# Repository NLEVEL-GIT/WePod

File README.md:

# WePod

Wepod is Our Ipod, it is an open source MP3 Player that uses the Xiao RP2040

PS: All images of the PCB, CAD and Schematics are on the assets folder if u wanna see.

## Features:
- 1.3 Inch TFT Display
- 5 Button
- SD Card Reader
- 3.5mm Jack
- Powered by any 5V Supply using the dedicated pads

## CAD Model:
Everything fits in a sandwich kind of way by stacking the bottom and top case parts and inbetween the PCB. It requires 4 M3x3 brass inserts and 4 15mm M3 Screws.
It has 3 different printed pieces. The Bottom part of the case where everything will sit in. The Top part that locks everything and the Butons (5 Needed).
Made in Fusion360 cuz its free.

## PCB
It was made in KiCad. Only needing to add Kicad Care package Symbols and Footprints for the Xiao RP2040 and a bunch of other symbols found in SnapEDA.
All 3D models were found on GrabCad

**Schematic:**

**PCB Layout:**

## Firmware Overview
The WePod uses C++ as its language of choice and it was made with the help of generative AI since im not really good at coding.

## BOM:
Here should be everything you need to make this hackpad

- 1.3 Inch TFT display
- DFPlayer
- 3.5mm Jack
- 5x 6x6mm buttons
- 1x XIAO RP2040
- 1x Case (3 printed parts)
- A Bunch of Resistors (1k, 3.3k, 6.8k, 10k and 100k)
- 2x 10uf Capacitors

## Extra stuff
This was my first Original project since my first was the MacroPad so not using a siplified code made me want to die. Conclusion: Hardware is life and coding Sucks

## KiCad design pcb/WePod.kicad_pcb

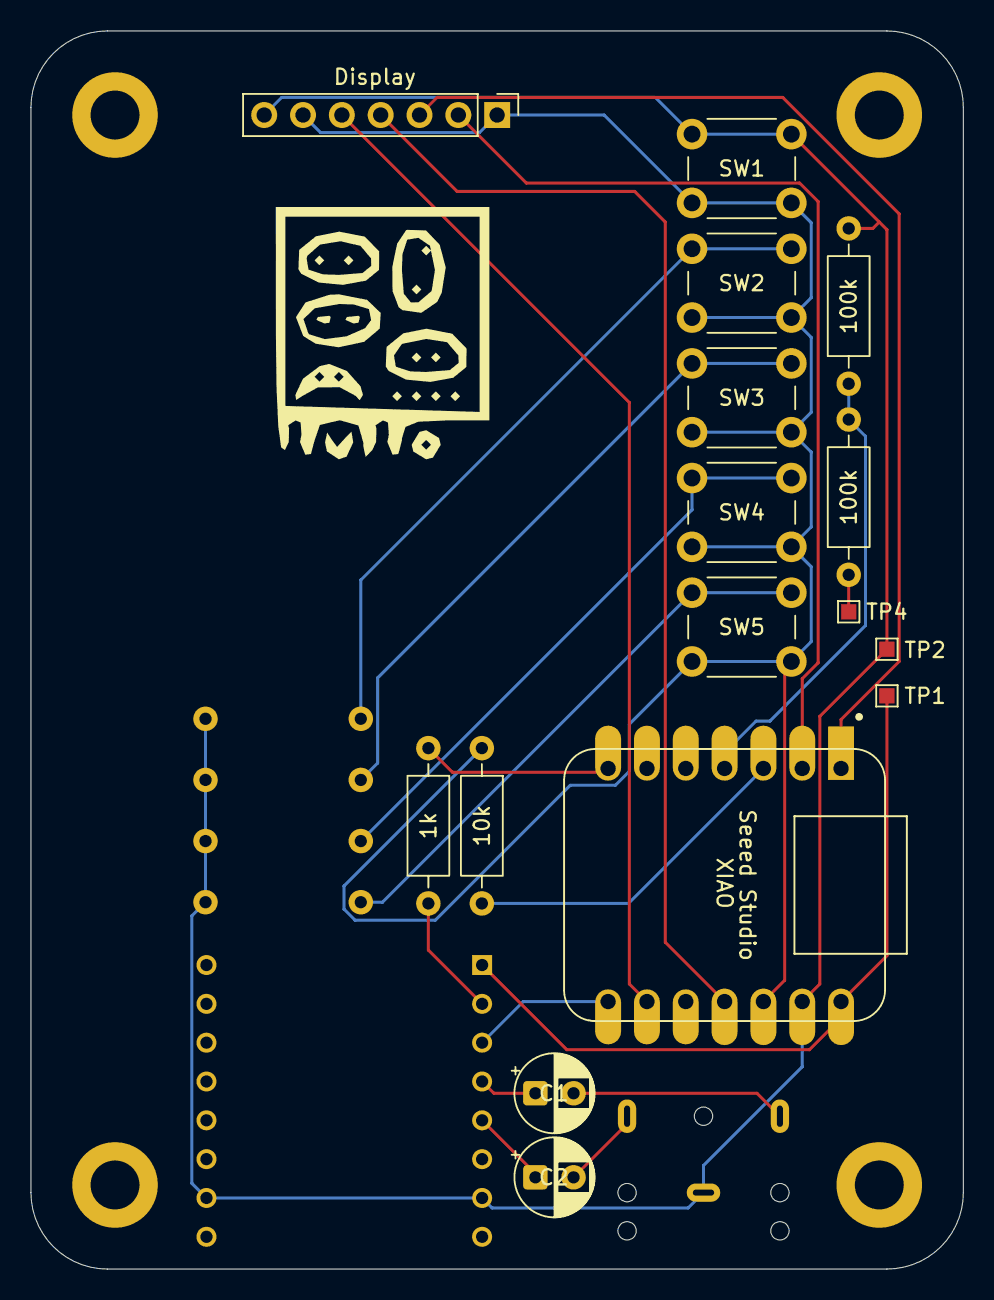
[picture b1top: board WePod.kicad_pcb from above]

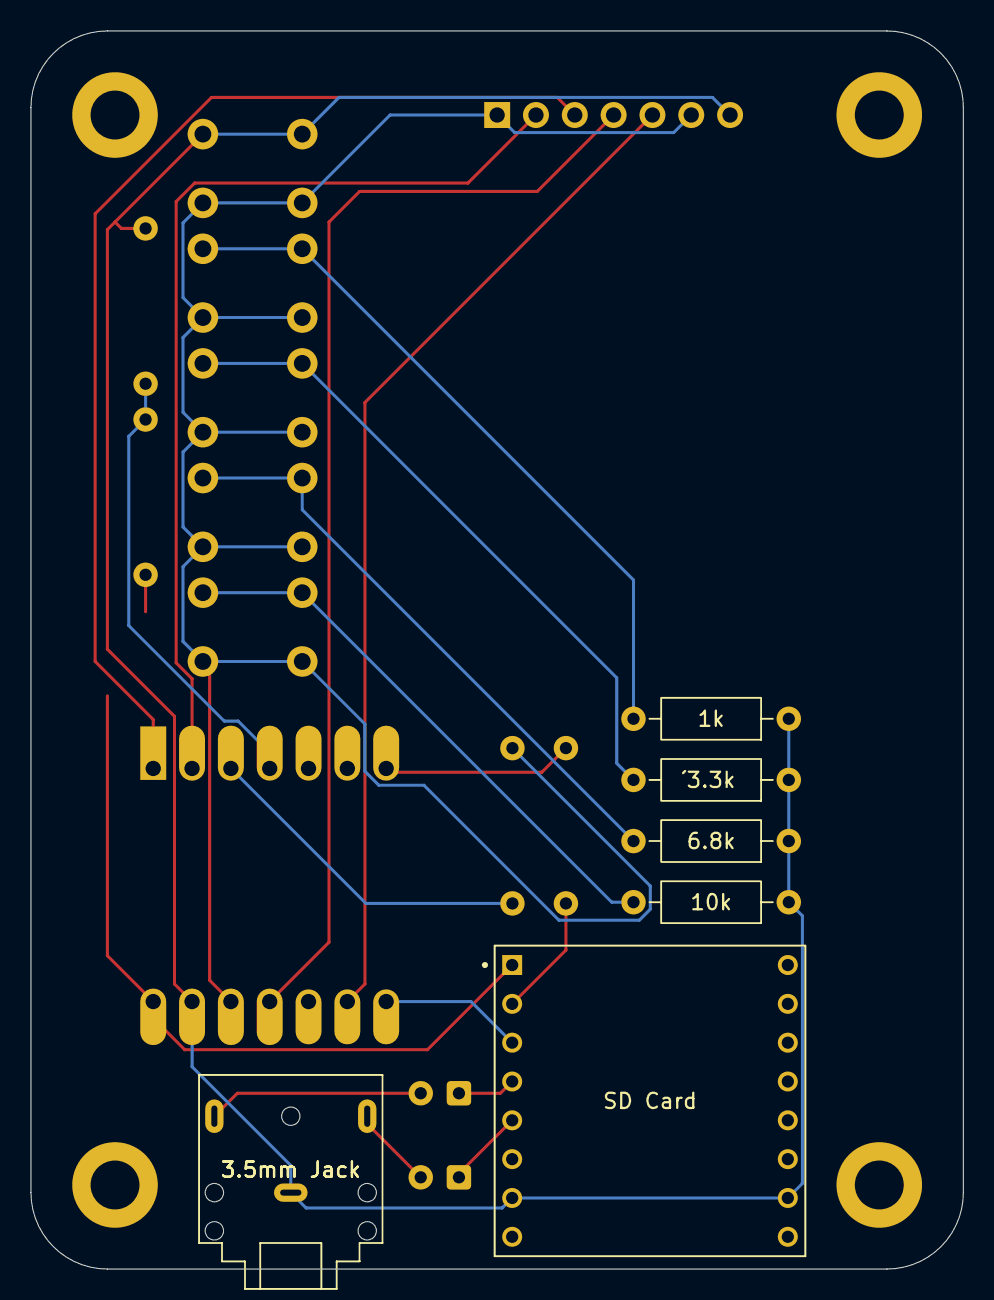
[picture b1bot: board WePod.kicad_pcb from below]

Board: 2 copper layers, 61.0 x 81.0 mm, 22 parts (6 on the bottom side), 21 nets.

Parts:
1k, 1k#2: 1k; R_Axial_DIN0207_L6.3mm_D2.5mm_P10.16mm_Horizontal
3.5mm Jack: 3.5mm Jack; Jack_3.5mm_CUI_SJ1-3523N_Horizontal
6.8k: 6.8k; R_Axial_DIN0207_L6.3mm_D2.5mm_P10.16mm_Horizontal
10k, 10k#2: 10k; R_Axial_DIN0207_L6.3mm_D2.5mm_P10.16mm_Horizontal
100k, 100k#2: 100k; R_Axial_DIN0207_L6.3mm_D2.5mm_P10.16mm_Horizontal
C1, C2: C; CP_Radial_D5.0mm_P2.50mm
J1: Display; PinHeader_1x07_P2.54mm_Vertical
SW1, SW2, SW3, SW4, SW5: SW_Push; SW_PUSH_6mm
TP1, TP2, TP4: TestPoint; TestPoint_Pad_1.0x1.0mm
U1: MOUDLE-SEEEDUINO-XIAO; XIAO-Generic-Hybrid-14P-2.54-21X17.8MM
U2: SD Card; MODULE_DFR0299
´3.3k: 3.3k; R_Axial_DIN0207_L6.3mm_D2.5mm_P10.16mm_Horizontal

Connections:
GND: 1k#2.1, 3.5mm Jack.S, 6.8k.1, 10k#2.1, 100k#2.2, J1.7, SW1.1, TP2.1 (1_1), U1.13 (GND), U2.7 (GND), U2.10 (GND), ´3.3k.1
unnamed: 3.5mm Jack.R, C1.2
unnamed: 3.5mm Jack.T, C2.2
unnamed: 10k.1, J1.1, J1.6, SW1.2, SW2.2, SW3.2, SW4.2, SW5.2, U1.12 (3V3)
unnamed: J1.2, U1.2 (PA4_A1_D1)
unnamed: J1.3, U1.1 (PA02_A0_D0)
unnamed: J1.4, U1.11 (PA6_A10_D10_MOSI)
unnamed: J1.5, U1.9 (PA7_A8_D8_SCK)
unnamed: 1k#2.2, SW2.1
unnamed: SW3.1, ´3.3k.2
unnamed: 6.8k.2, SW4.1
unnamed: 10k#2.2, SW5.1
unnamed: 100k.1, TP4.1 (1_1)
unnamed: 10k.2, U1.3 (PA10_A2_D2)
unnamed: 100k.2, 100k#2.1, U1.4 (PA11_A3_D3)
unnamed: 1k.1, U1.7 (PB08_A6_D6_TX)
unnamed: U1.8 (PB09_A7_D7_RX), U2.3 (TX)
unnamed: C2.1, U2.5 (DAC_L)
unnamed: C1.1, U2.4 (DAC_R)
unnamed: 1k.2, U2.2 (RX)
VCC: TP1.1 (1_1), U1.14 (5V), U2.1 (VCC)
